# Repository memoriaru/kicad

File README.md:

# kicad

Rust toolchain for programmatic KiCad design: parse, generate, and render.

| Crate | What it does |
| --- | --- |
| [kicad-json5](kicad-json5/) | KiCad S-expression ↔ JSON5 bidirectional compiler for schematics and PCBs (KiCad 7–10), with topology extraction and board-level auto-layout |
| [kicad-render](kicad-render/) | Schematic & PCB SVG renderer — a 1:1 Rust port of the [KiCanvas](https://github.com/theacodes/kicanvas) painters, with PDF/PNG output |

Both crates are MIT licensed. `kicad-render` derives from KiCanvas
(© 2022 Alethea Katherine Flowers) and ecad-viewer
(© 2024 深圳华秋电子有限公司), both MIT — see its [LICENSE](kicad-render/LICENSE).

## Quick start

```sh
cargo build --release

# Convert a KiCad board to JSON5 and back
./target/release/kicad-json5 input.kicad_pcb -o board.json5
./target/release/kicad-json5 board.json5 -o roundtrip.kicad_pcb

# Render a schematic to SVG
./target/release/kicad-render input.kicad_sch -o schematic.svg
```

## Development

```sh
cargo test --workspace          # runs on committed fixtures, no external files needed
cargo clippy --workspace --all-targets -- -D warnings
```

Real-world boards/schematics from the HQ EDA (华秋 EDA) online viewer demo set
are exercised by opt-in tests: `KICAD_DEMO_DIR=/path/to/demo cargo test -- --ignored`
(see `*/tests/fixtures/README.md`).

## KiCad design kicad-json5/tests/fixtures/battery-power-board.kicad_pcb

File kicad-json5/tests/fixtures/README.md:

# Test Fixtures

All fixtures in this directory are generated by this toolchain itself
(`generator` field: `kicad-json5` / `component-db`) and are safe to redistribute.

| File | What it exercises |
| --- | --- |
| `ch340g-usb-uart.kicad_pcb` | Small 2-layer board: footprints, pads, zones, graphics, nets |
| `battery-power-board.kicad_pcb` | 2-layer power board: zones + Edge.Cuts graphics |
| `battery-power-board.kicad_sch` | Schematic produced by the JSON5 → S-expression path |
| `battery-power-board-auto-layout.json5` | JSON5 board-level auto-layout input |

## Optional: HQ EDA demo files

Some `#[ignore]`d integration tests additionally exercise large real-world
boards/schematics from the HQ EDA (华秋 EDA) online ECAD viewer demo set.
These files are **not redistributable** and are therefore not committed.
Download them from the HQ EDA demo page and place them into a directory of
your choice, then run:

```sh
KICAD_DEMO_DIR=/path/to/dir cargo test -- --ignored
```

If the variable is unset, the default lookup path is `../example_sch`
(the layout used during development).

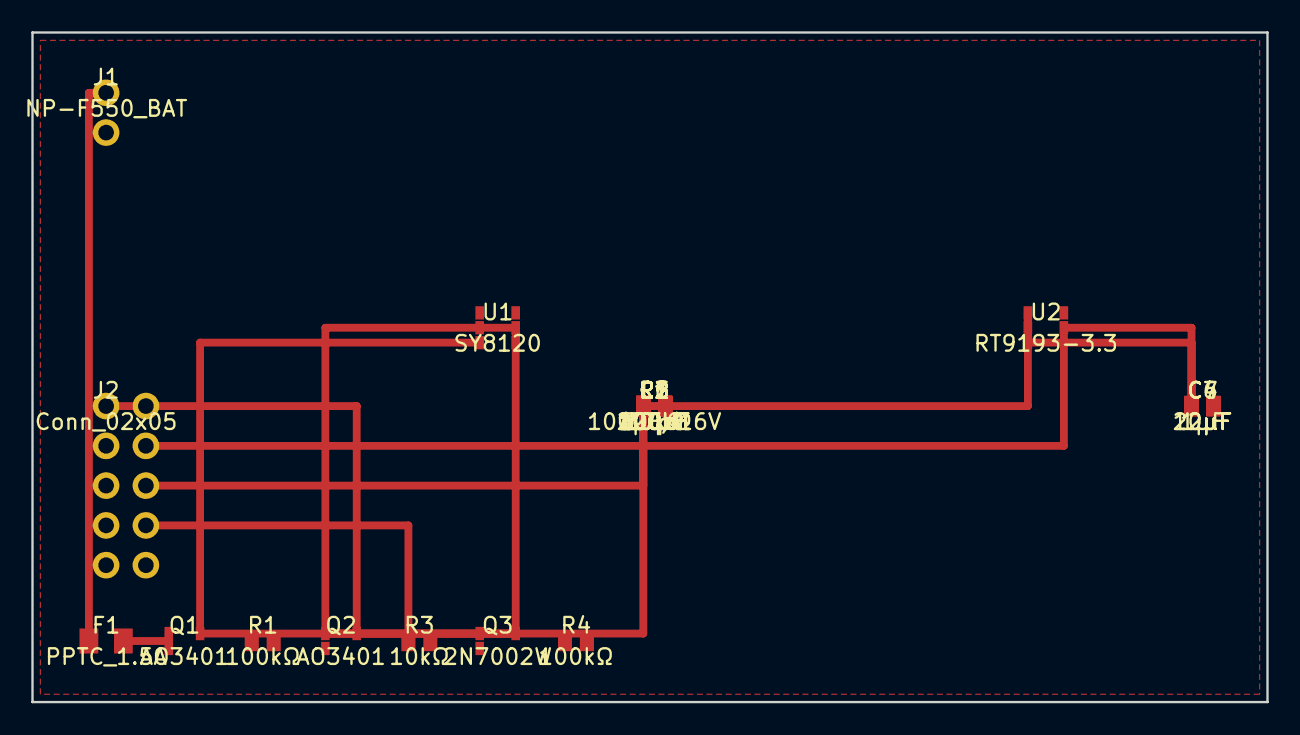
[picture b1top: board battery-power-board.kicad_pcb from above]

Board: 2 copper layers, 78.9 x 42.8 mm, 22 parts (0 on the bottom side), 13 nets.

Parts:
C1: 100μF/16V; CP_Elec_6.3x7.7
C2: 100nF; C_0805_2012Metric
C3, C7: 10μF; C_0805_2012Metric
C4: 22μF; C_0805_2012Metric
C5: 100nF; C_0402_1005Metric
C6: 1μF; C_0805_2012Metric
F1: PPTC_1.5A; Fuse_1206_3216Metric
J1: NP-F550_BAT; PinHeader_1x02_P2.54mm_Vertical
J2: Conn_02x05; PinHeader_2x05_P2.54mm_Vertical
L1: 4.7μH; L_4020_1005Metric
Q1, Q2: AO3401; SOT-23
Q3: 2N7002W; SOT-323
R1, R2, R4: 100kΩ; R_0805_2012Metric
R3: 10kΩ; R_0805_2012Metric
R5: 220kΩ; R_0805_2012Metric
R6: 30kΩ; R_0805_2012Metric
U1: SY8120; SOT-23-6
U2: RT9193-3.3; SOT-23-5

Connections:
3V3_STBY: J2.7, R3.1
5V_BUCK: C7.1, J2.3, U2.5
BST_NODE: R5.2, R6.1, U1.6
CCD_PWR_EN: C5.1, L1.1, U1.3
FB_NODE: Q2.1, Q3.3, R2.2
GATE_Q1: Q3.1, R3.2, R4.1
GATE_Q2: Q1.1, R1.1
GND: F1.1, J1.1
SW_NODE: C5.2, U1.4
VBAT_7V4: C4.1, C6.1, J2.5, L1.2, R5.1, U2.1, U2.3
VBAT_FUSED: C1.1, C2.1, C3.1, Q1.3, Q2.2, R2.1, U1.1, U1.5
VBAT_IN: F1.2, Q1.2
VBAT_PROT: J2.1, Q2.3

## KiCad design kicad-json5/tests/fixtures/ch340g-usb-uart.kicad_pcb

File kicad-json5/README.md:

# kicad-json5

KiCad 原理图 S-expression 与 JSON5 的双向编译器，同时支持电路拓扑提取。为 AI 辅助电路设计提供人机友好的中间表示。

## 为什么用 JSON5？

- **人类可读** — 支持注释、无引号键名、尾逗号
- **Token 高效** — 比 S-expression 少 40-50% 的 token
- **AI 友好** — 结构清晰，LLM 可直接理解和生成
- **双向转换** — `.kicad_sch` ↔ `.json5` 完整 round-trip

## 安装

```bash
cargo build --release
# 二进制: target/release/kicad-json5
```

## CLI 用法

### 基本转换

```bash
# S-expression → JSON5
kicad-json5 schematic.kicad_sch -o schematic.json5

# JSON5 → S-expression
kicad-json5 schematic.json5 -o schematic.kicad_sch

# 输出到 stdout
kicad-json5 schematic.kicad_sch
```

### 全部选项

| 选项 | 说明 |
|------|------|
| `-o, --output <FILE>` | 输出文件路径 |
| `-f, --format <FORMAT>` | 输出格式：`json5`、`sexpr`、`topology` |
| `-i, --indent <N>` | 缩进空格数（默认 2） |
| `--kicad-version <V>` | 目标 KiCad 版本：7, 8, 9, 10+ |
| `--no-comments` | JSON5 输出不含注释 |
| `--validate` | 仅验证，不输出 |
| `--debug-ast` | 打印 AST 用于调试 |
| `--power-flags` | JSON5→Sexpr 时自动插入 PWR_FLAG |
| `--dialect <D>` | `.kicad_pcb` 输出方言：`official`（默认, stock kicad-cli 可直接加载）/ `huaqiu`（华秋 fork 兼容）/ `auto`（按输入内容探测, 往返保真） |
| `-v, --verbose` | 详细输出 |

### 示例

```bash
# JSON5 → KiCad，自动插入 PWR_FLAG 和 NC 标记
kicad-json5 carrier-board.json5 -o carrier-board.kicad_sch --power-flags

# 提取电路拓扑
kicad-json5 schematic.kicad_sch -f topology -o topology.json

# 仅验证
kicad-json5 schematic.kicad_sch --validate
```

## JSON5 输入格式

```json5
{
  // 原理图元数据
  version: "20241129",
  generator: "kicad-json5",

  title_block: {
    title: "CCD Carrier Board",
    date: "2026-04-01",
    paper: "A3",
  },

  // 元件实例
  components: [
    {
      ref: "U1",
      lib_id: "Device:R",
      value: "10k",
      position: { x: 100, y: 50, rotation: 0 },
      pins: {
        "1": { net_id: 1, net_name: "VCC" },
        "2": { net_id: 5, net_name: "SDA" },
      },
    },
    {
      ref: "U3",
      lib_id: "custom:ME2802",
      value: "ME2802",
      position: { x: 39.37, y: 110.49, rotation: 0 },
      pins: {
        "1": { net_name: "GND" },
        "2": { net_name: "VOUT_5V" },
        "3": { net_name: "VBAT" },
        "4": { nc: true },   // No-Connect 标记
      },
    },
  ],

  // 网络定义
  nets: [
    { id: 0, name: "GND" },
    { id: 1, name: "VCC" },
    { id: 5, name: "SDA" },
  ],
}
```

## 核心特性

### 标准 Device 库嵌入

内置 KiCad 标准 Device 库常用符号（R, C, L, D, LED, NTC），生成 `.kicad_sch` 时自动嵌入 lib_symbol 定义，无需外部库文件即可通过 ERC。

### 自动标签生成

JSON5→S-expression 时，自动为每个网络连接点生成 `global_label`，放置在引脚连接点的世界坐标位置，确保 KiCad 正确识别网络连通性。

### PWR_FLAG 自动插入

配合 `--power-flags` 选项，自动检测需要电源标记的网络（有 `power_in` 引脚但无 `power_out` 驱动），插入符合 KiCad 官方 `power.kicad_sym` 规范的 PWR_FLAG 符号。

> **已知限制（层次原理图）：** `--power-flags` 仅对无子图的单文件（flat）原理图生效。包含 `sheets` 的层次原理图中，同一 global power net 上的多个 PWR_FLAG 会触发 KiCad ERC `pin_to_pin` 冲突。层次原理图的子图需手动在 KiCad 中添加 PWR_FLAG，或通过 power symbol（如 VCC/GND symbol，自带 `power_out` 引脚）隐式驱动电源网络。

### No-Connect 标记

引脚声明 `"nc": true` 后，在对应引脚位置生成 `(no_connect ...)` 元素，消除 KiCad ERC 的 `pin_not_connected` 警告。

### 拓扑提取

`-f topology` 模式提取电路语义信息：
- 电源域和地线网络识别
- 信号路径追踪
- 功能模块识别（上拉电阻、去耦电容、LED 指示等）

## 项目结构

```
kicad-json5/
├── src/
│   ├── lexer/              # S-expression 分词器
│   │   ├── mod.rs
│   │   ├── token.rs
│   │   └── scanner.rs
│   ├── parser/             # 解析器
│   │   ├── mod.rs
│   │   ├── ast.rs
│   │   ├── schematic.rs    # S-expression → IR
│   │   ├── json5_parser.rs # JSON5 → IR
│   │   └── s_expr_parser.rs
│   ├── ir/                 # 中间表示
│   │   ├── schematic.rs    # 原理图整体结构
│   │   ├── component.rs    # 元件/引脚实例
│   │   ├── net.rs          # 网络/标签/NC
│   │   └── symbol.rs       # 库符号定义
│   ├── codegen/            # 代码生成
│   │   ├── json5_gen.rs    # IR → JSON5
│   │   ├── sexpr_gen/      # IR → S-expression
│   │   │   ├── mod.rs
│   │   │   ├── auto.rs     # 自动 wire/label/PWR_FLAG 生成
│   │   │   ├── element.rs  # 元件实例生成
│   │   │   ├── graphic.rs  # 图形元素生成
│   │   │   └── symbol.rs   # 库符号嵌入
│   │   └── standard_symbols.rs  # 嵌入式标准符号
│   ├── topology/           # 拓扑分析
│   │   ├── extractor.rs    # 拓扑提取主逻辑
│   │   ├── classify.rs     # 元件分类
│   │   ├── connectivity.rs # 连通性分析
│   │   ├── patterns.rs     # 电路模式识别
│   │   ├── summary.rs      # 拓扑摘要
│   │   └── types.rs        # 拓扑数据类型
│   ├── lib.rs
│   ├── main.rs             # CLI 入口
│   └── error.rs
├── tests/                  # 集成测试
│   ├── fixtures/           # 测试 fixture（本工具链自产，可再分发）
│   ├── board_roundtrip.rs  # PCB IR / JSON5 / sexpr 往返
│   ├── roundtrip.rs        # PCB 元素计数回归
│   ├── sch_roundtrip.rs    # 原理图解析与往返
│   └── layout_test.rs      # 板级自动布局
└── CHANGELOG.md
```

## 依赖

- `clap` — CLI 参数解析
- `serde` / `serde_json` / `serde_json5` — 序列化
- `uuid` — UUID 生成
- `thiserror` / `anyhow` — 错误处理

## License

MIT

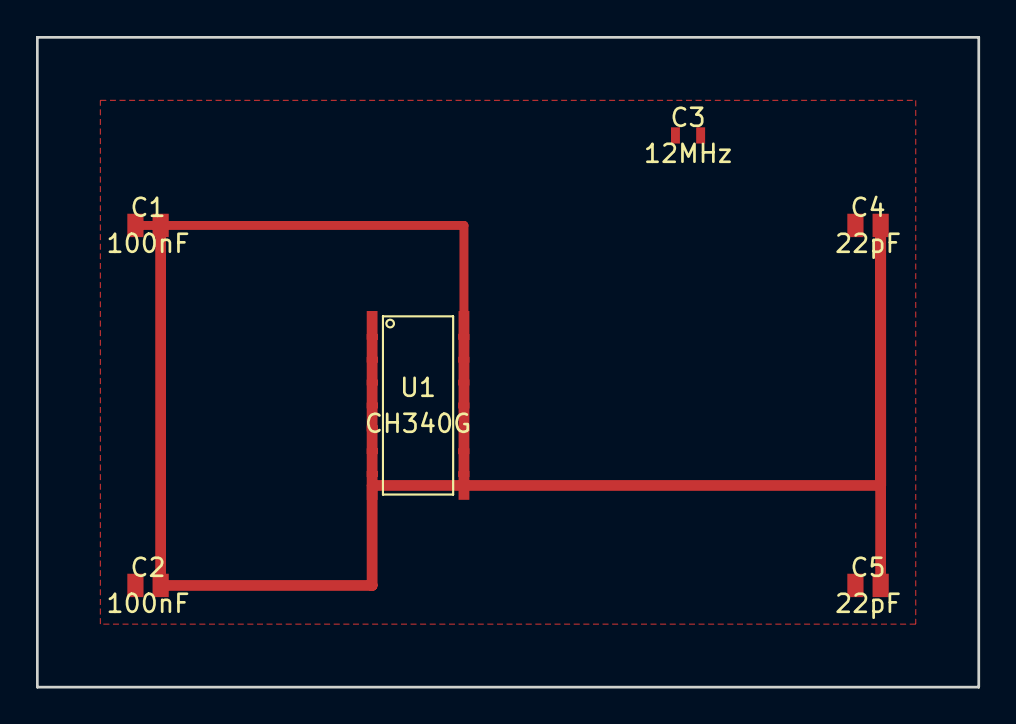
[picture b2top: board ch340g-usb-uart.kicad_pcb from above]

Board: 2 copper layers, 52.3 x 36.1 mm, 6 parts (0 on the bottom side), 4 nets.

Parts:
C1, C2: 100nF; C_0805_2012Metric
C3: 12MHz; Crystal_SMD_3225-4Pin_3.2x2.5mm
C4, C5: 22pF; C_0805_2012Metric
U1: CH340G; SOP-16_3.9x9.9mm_P1.27mm

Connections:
GND: C1.2, C2.2, C4.2, C5.2, U1.1 (GND)
VCC: C1.1, U1.16 (VCC)
XI: C3.1, C4.1
XO: C3.2, C5.1

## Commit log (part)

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2026-05-03 🔧 chore: add test fixture schematics, remove docs from tracking
    - Add 5 real .kicad_sch files used by kicad-json5/kicad-render tests
    - Remove docs/ from git tracking (local only)
2026-05-03 🔧 chore: add Apache 2.0 LICENSE
2026-05-03 📝 docs: restore local docs to git tracking
2026-05-03 🔥 chore: remove footprints from remote tracking
2026-05-03 ✨ init: kicad-json5 + kicad-render
    - kicad-json5: KiCad S-expression ↔ JSON5 bidirectional compiler
    - kicad-render: KiCad schematic SVG renderer (1:1 port from KiCanvas)
    - example_sch/: test fixture schematics
2026-05-03 🔧 chore: add LICENSE and test fixture schematics
2026-05-03 🔥 chore: remove non-fixture files from example_sch
2026-05-03 📝 docs: add bilingual README for kicad-rs repo
2026-05-03 📝 docs: change license from Apache 2.0 to MIT
2026-05-03 📝 docs: add MIT LICENSE file
